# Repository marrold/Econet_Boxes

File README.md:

# Econet Boxes

A collection of boxes, couplers, hubs, joiners, and other stuff for a BBC / Acorn Econet Network

**Note:** Currently untested

## License

- This project is licensed under the MIT license

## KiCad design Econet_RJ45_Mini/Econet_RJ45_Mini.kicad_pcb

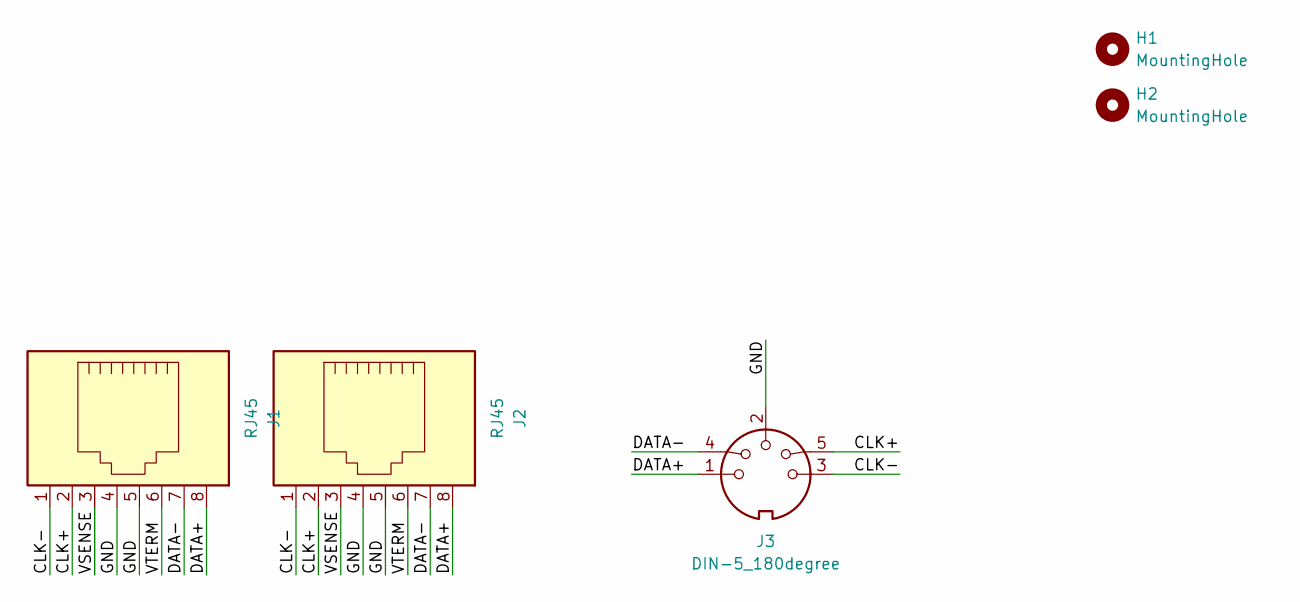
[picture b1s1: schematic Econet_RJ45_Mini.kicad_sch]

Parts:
H1, H2: MountingHole; MountingHole_3.2mm_M3
J1, J2: RJ45; RJ45_Vertical
J3: DIN-5_180degree; DIN5

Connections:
/CLK+: J1.2, J2.2, J3.5
/CLK-: J1.1, J2.1, J3.3
/DATA+: J1.8, J2.8, J3.1
/DATA-: J1.7, J2.7, J3.4
/GND: J1.4, J1.5, J2.4, J2.5, J3.2
/VSENSE: J1.3, J2.3
/VTERM: J1.6, J2.6

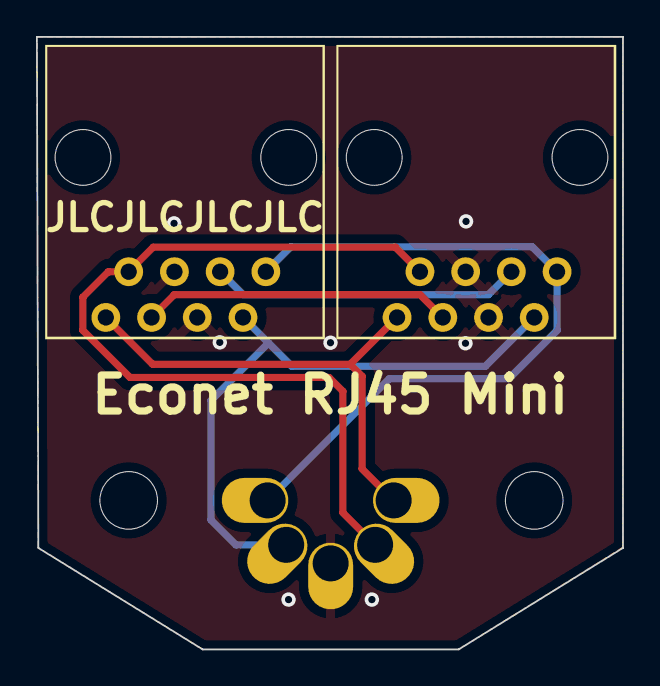
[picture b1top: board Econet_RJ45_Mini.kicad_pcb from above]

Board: 2 copper layers, 32.6 x 34.0 mm, 5 parts (1 on the bottom side), 7 nets.

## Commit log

2024-01-24 Init
2024-02-02 Make DIN connector bigger to increase tolerances
